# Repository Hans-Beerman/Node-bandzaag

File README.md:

**NodeStandard**

Node bandzaag is based on the standard node, and is used at the MakerSpace Leiden, to control the bandzaag. This repository has the following subdirs:

- **Drawings:**

Schematic of the wiring between the different modules used

- **KiCad\_files:**

The design of the PCB for the Node/Controller. De PCB in this design is not meant to be used for a real PCB. It is used as guideline for a handmade PCB

- **Photos:**

Some photos of the Node made.

- **PlatformIO\_Files:**

The source code for the Node and the display used. For the development of this software PlatformIO is used. PlatformIO is an Extension on Visual Studio Code.

Currently some of the directories are empty, because the node is not ready yet.

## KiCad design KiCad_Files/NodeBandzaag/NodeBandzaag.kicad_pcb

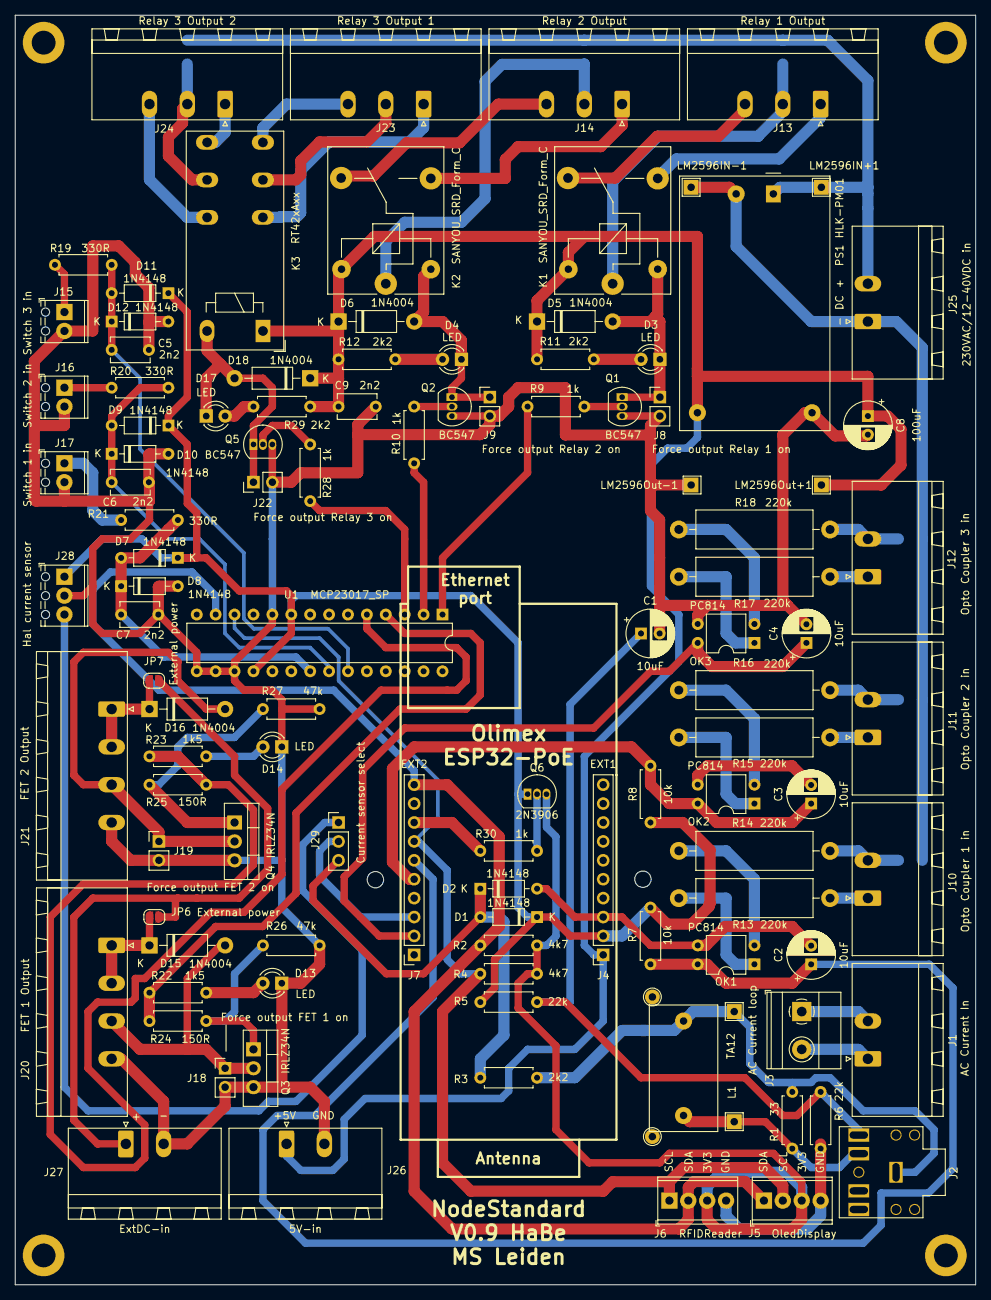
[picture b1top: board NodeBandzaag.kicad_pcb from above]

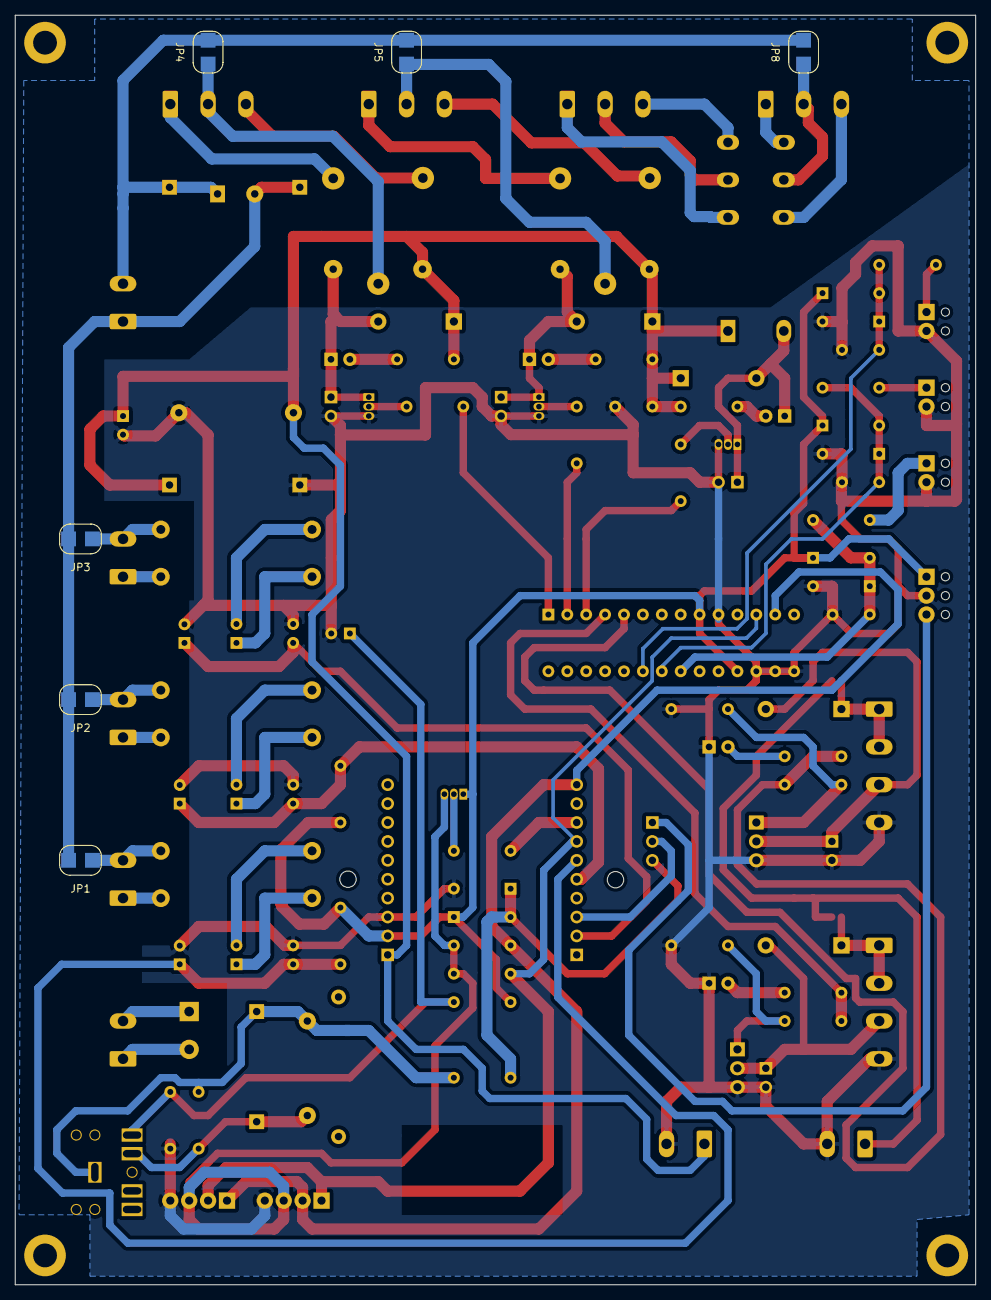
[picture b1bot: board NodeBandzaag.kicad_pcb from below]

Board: 2 copper layers, 129.0 x 170.6 mm, 115 parts (6 on the bottom side), 74 nets.

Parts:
C1, C2, C3, C4: 10uF; CP_Radial_D6.3mm_P2.50mm
C5, C6, C7, C9: 2n2; C_Disc_D5.1mm_W3.2mm_P5.00mm
C8: 100uF; CP_Radial_D6.3mm_P2.50mm
D1, D2, D7, D8, D9, D10, D11, D12: 1N4148; D_DO-35_SOD27_P7.62mm_Horizontal
D3, D4, D13, D14, D17: LED; LED_D3.0mm
D5, D6, D15, D16, D18: 1N4004; D_DO-41_SOD81_P10.16mm_Horizontal
J1: AC Current In; PhoenixContact_MSTB_2,5_2-GF-5,08_1x02_P5.08mm_Horizontal_T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
J2: Current coil in; Jack_3.5mm_CUI_FEMPM_Horizontal
J3: AC Current loop; TerminalBlock_Phoenix_MKDS-1,5-2-5.08_1x02_P5.08mm_Horizont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
J4: EXT1; PinSocket_1x10_P2.54mm_Vertical
J5: OledDisplay; TerminalBlock_Phoenix_MPT-0,5-4-2.54_1x04_P2.54mm_Horizontal
J6: RFIDReader; TerminalBlock_Phoenix_MPT-0,5-4-2.54_1x04_P2.54mm_Horizontal
J7: EXT2; PinSocket_1x10_P2.54mm_Vertical
J8: Force output Relay 1 on; PinHeader_1x02_P2.54mm_Vertical
J9: Force output Relay 2 on; PinHeader_1x02_P2.54mm_Vertical
J10: Opto Coupler 1 in; PhoenixContact_MSTB_2,5_2-GF-5,08_1x02_P5.08mm_Horizontal_T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
J11: Opto Coupler 2 in; PhoenixContact_MSTB_2,5_2-GF-5,08_1x02_P5.08mm_Horizontal_T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
J12: Opto Coupler 3 in; PhoenixContact_MSTB_2,5_2-GF-5,08_1x02_P5.08mm_Horizontal_T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
J13: Relay 1 Output; PhoenixContact_MSTB_2,5_3-GF-5,08_1x03_P5.08mm_Horizontal_T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
J14: Relay 2 Output; PhoenixContact_MSTB_2,5_3-GF-5,08_1x03_P5.08mm_Horizontal_T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
J15: Switch 3 in; TerminalBlock_Phoenix_MPT-0,5-2-2.54_1x02_P2.54mm_Horizontal
J16: Switch 2 in; TerminalBlock_Phoenix_MPT-0,5-2-2.54_1x02_P2.54mm_Horizontal
J17: Switch 1 in; TerminalBlock_Phoenix_MPT-0,5-2-2.54_1x02_P2.54mm_Horizontal
J18: Force output FET 1 on; PinHeader_1x02_P2.54mm_Vertical
J19: Force output FET 2 on; PinHeader_1x02_P2.54mm_Vertical
J20: FET 1 Output; PhoenixContact_MSTB_2,5_4-GF-5,08_1x04_P5.08mm_Horizontal_T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
J21: FET 2 Output; PhoenixContact_MSTB_2,5_4-GF-5,08_1x04_P5.08mm_Horizontal_T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
J22: Force output Relay 3 on; PinHeader_1x02_P2.54mm_Vertical
J23: Relay 3 Output 1; PhoenixContact_MSTB_2,5_3-GF-5,08_1x03_P5.08mm_Horizontal_T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
J24: Relay 3 Output 2; PhoenixContact_MSTB_2,5_3-GF-5,08_1x03_P5.08mm_Horizontal_T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
J25: 230VAC/12-40VDC in; PhoenixContact_MSTB_2,5_2-GF-5,08_1x02_P5.08mm_Horizontal_T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
J26: 5V-in; PhoenixContact_MSTB_2,5_2-GF-5,08_1x02_P5.08mm_Horizontal_T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
J27: ExtDC-in; PhoenixContact_MSTB_2,5_2-GF-5,08_1x02_P5.08mm_Horizontal_T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
J28: Hal current sensor; TerminalBlock_Phoenix_MPT-0,5-3-2.54_1x03_P2.54mm_Horizontal
J29: Current sensor select; PinHeader_1x03_P2.54mm_Vertical
JP1, JP2, JP3: 230VAC-N; SolderJumper-2_P3mm_Open_RoundedPad
JP4, JP5, JP8: 230VAC-L; SolderJumper-2_P3mm_Open_RoundedPad
JP6, JP7: External power; SolderJumper-2_P1.3mm_Open_RoundedPad1.0x1.5mm
K1, K2: SANYOU_SRD_Form_C; Relay_SPDT_SANYOU_SRD_Series_Form_C
K3: RT42xAxx; Relay_DPDT_Schrack-RT2-FormC_RM5mm
L1: TA12; TA12-100
LM2596IN+1: IN+; TestPoint_THTPad_2.0x2.0mm_Drill1.0mm
LM2596IN-1: IN-; TestPoint_THTPad_2.0x2.0mm_Drill1.0mm
LM2596Out+1: Out+; TestPoint_THTPad_2.0x2.0mm_Drill1.0mm
LM2596Out-1: OUT-; TestPoint_THTPad_2.0x2.0mm_Drill1.0mm
OK1, OK2, OK3: PC814; DIP-4_W7.62mm
PS1: HLK-PM01; Converter_ACDC_HiLink_HLK-PMxx
Q1, Q2, Q5: BC547; TO-92_Inline
Q3, Q4: IRLZ34N; TO-220-3_Vertical
Q6: 2N3906; TO-92_Inline
R1: 33; R_Axial_DIN0207_L6.3mm_D2.5mm_P7.62mm_Horizontal
R2, R4: 4k7; R_Axial_DIN0207_L6.3mm_D2.5mm_P7.62mm_Horizontal
R3, R11, R12, R29: 2k2; R_Axial_DIN0207_L6.3mm_D2.5mm_P7.62mm_Horizontal
R5, R6: 22k; R_Axial_DIN0207_L6.3mm_D2.5mm_P7.62mm_Horizontal
R7, R8: 10k; R_Axial_DIN0207_L6.3mm_D2.5mm_P7.62mm_Horizontal
R9, R10, R28, R30: 1k; R_Axial_DIN0207_L6.3mm_D2.5mm_P7.62mm_Horizontal
R13, R14, R15, R16, R17, R18: 220k; R_Axial_DIN0516_L15.5mm_D5.0mm_P20.32mm_Horizontal
R19, R20, R21: 330R; R_Axial_DIN0207_L6.3mm_D2.5mm_P7.62mm_Horizontal
R22, R23: 1k5; R_Axial_DIN0207_L6.3mm_D2.5mm_P7.62mm_Horizontal
R24, R25: 150R; R_Axial_DIN0207_L6.3mm_D2.5mm_P7.62mm_Horizontal
R26, R27: 47k; R_Axial_DIN0207_L6.3mm_D2.5mm_P7.62mm_Horizontal
TP5: La; TestPoint_THTPad_2.0x2.0mm_Drill1.0mm
TP6: Lb; TestPoint_THTPad_2.0x2.0mm_Drill1.0mm
U1: MCP23017_SP; DIP-28_W7.62mm

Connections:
230VAC-L: J25.2, JP4.2, JP5.2, JP8.2, LM2596IN+1.1, PS1.1
230VAC-N: J25.1, JP1.2, JP2.2, JP3.2, LM2596IN-1.1, PS1.2
+3V3: D1.1, D7.1, D9.1, D11.1, J4.2, J28.1, Q6.1, R5.1, R7.1, R8.1, U1.9, U1.18
+5V: C8.1, C9.1, D5.1, D6.1, D18.1, J4.1, J26.1, K1.5, K2.5, K3.A1, LM2596Out+1.1, PS1.4, R11.1, R12.1, R29.1
ExternalDCPower: J27.1, JP6.1, JP7.1
FET1: R22.1, R24.2, U1.4
FET2: R23.1, R25.2, U1.5
GND: C1.2, C2.2, C3.2, C4.2, C5.2, C6.2, C7.2, C8.2, C9.2, D2.2, D8.2, D10.2, D12.2, D13.1, D14.1, J4.3, J5.4, J6.4, J8.2, J9.2, J15.2, J16.2, J17.2, J18.2, J19.2, J20.4, J21.4, J22.2, J26.2, J27.2, J28.2, LM2596Out-1.1, OK1.3, OK2.3, OK3.3, PS1.3, Q1.3, Q2.3, Q3.3, Q4.3, Q5.3, R6.2, R26.2, R27.2, U1.10, U1.15, U1.16, U1.17
GPI35: J7.3, J29.2
GPI36_U1RXD: C4.1, J7.2, OK3.4
GPIO13_I2C-SDA: J5.1, J6.2, J7.10, R2.2, U1.13
GPIO15_HS2_CMD: J7.8, R30.1
GPIO16_I2C-SCL: J5.2, J6.1, J7.7, R4.2, U1.12
GPIO32: C2.1, J7.6, OK1.4, R7.2
GPIO33: C3.1, J7.5, OK2.4, R8.2
unnamed: C1.1, J2.T, R5.2, R6.1
unnamed: D1.2, D2.1, J29.3, R3.1
unnamed: D3.1, D5.2, J8.1, K1.2, Q1.1
unnamed: D3.2, R11.2
unnamed: D4.1, D6.2, J9.1, K2.2, Q2.1
unnamed: D4.2, R12.2
unnamed: D13.2, R22.2
unnamed: D14.2, R23.2
unnamed: D15.1, J20.1, J20.2, JP6.2
unnamed: D15.2, J18.1, J20.3, Q3.2
unnamed: D16.1, J21.1, J21.2, JP7.2
unnamed: D16.2, J19.1, J21.3, Q4.2
unnamed: D17.1, D18.2, J22.1, K3.A2, Q5.1
unnamed: D17.2, R29.2
unnamed: J1.1, J3.2
unnamed: J1.2, J3.1
unnamed: J2.S, L1.2, R1.1, R3.2, TP6.1
unnamed: J2.TN, L1.1, R1.2, TP5.1
unnamed: J5.3, J6.3, Q6.3, R2.1, R4.1
unnamed: J10.1, R13.1
unnamed: J10.2, JP1.1, R14.1
unnamed: J11.1, R15.1
unnamed: J11.2, JP2.1, R16.1
unnamed: J12.1, R17.1
unnamed: J12.2, JP3.1, R18.1
unnamed: J13.1, K1.3
unnamed: J13.2, JP4.1, K1.1
unnamed: J13.3, K1.4
unnamed: J14.1, K2.3
unnamed: J14.2, JP5.1, K2.1
unnamed: J14.3, K2.4
unnamed: J15.1, R19.1
unnamed: J16.1, R20.1
unnamed: J17.1, R21.1
unnamed: J23.1, K3.12
unnamed: J23.2, K3.11
unnamed: J23.3, K3.14
unnamed: J24.1, K3.24
unnamed: J24.2, JP8.1, K3.21
unnamed: J24.3, K3.22
unnamed: J28.3, J29.1
unnamed: OK1.1, R13.2
unnamed: OK1.2, R14.2
unnamed: OK2.1, R15.2
unnamed: OK2.2, R16.2
unnamed: OK3.1, R17.2
unnamed: OK3.2, R18.2
unnamed: Q1.2, R9.1
unnamed: Q2.2, R10.1
unnamed: Q3.1, R24.1, R26.1
unnamed: Q4.1, R25.1, R27.1
unnamed: Q5.2, R28.1
unnamed: Q6.2, R30.2
Relay1: R9.2, U1.1
Relay2: R10.2, U1.2
Relay3: R28.2, U1.3
Switch1: C7.1, D7.2, D8.1, R21.2, U1.21
Switch2: C6.1, D9.2, D10.1, R20.2, U1.22
Switch3: C5.1, D11.2, D12.1, R19.2, U1.23

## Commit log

2021-12-08 First release of the Node bandzaag, node is not ready yet
2021-12-14 V1.0.0.0 Updated the KiCad design and added the source code for the node
2021-12-17 V1.0.0.1 added missing .pio directory.
2021-12-23 V1.0.1.0 Switching to machinestate NOTACTIVE from POWERED or ACTIVE if 230 V voltage on optocoupler is removed
2022-01-29 V1.0.2.0 Changed the behaviour and timing e.g. when bandsaw is switched off
2022-02-24 V1.0.4.0 Added to show software version in MQTT log and made some small improvements
2022-02-24 V1.0.4.0 Corrected some params for MS
2022-02-26 V1.0.5.0 Lowered CURRENT_TRESHOLD because low current was detected while bandsaw was running
